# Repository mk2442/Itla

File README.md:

# Itla

Repositorio de proyectos y prácticas.

## Estructura

| Carpeta | Contenido |
|---|---|
| `solid/` | Diseños en SolidWorks: piezas, ensambles, planos y archivos de impresión 3D |
| `electronica/` | Proyectos de electrónica: placa ESP32-DEVKITV1 (librerías y documentación), PHM-30A y carrito (KiCad) |
| `programacion-c/` | Ejercicios y prácticas en lenguaje C, organizados por capítulo y proyecto |
| `digital/` | Circuitos digitales: proyectos (Gowin, KiCad, Proteus, RC), impresión 3D y documentos de clase |
| `microcontroladores/` | Proyectos de microcontroladores: ESP-IDF (ESP32) y Arduino |

Los archivos de compilación, binarios y configuración local del IDE no se incluyen.

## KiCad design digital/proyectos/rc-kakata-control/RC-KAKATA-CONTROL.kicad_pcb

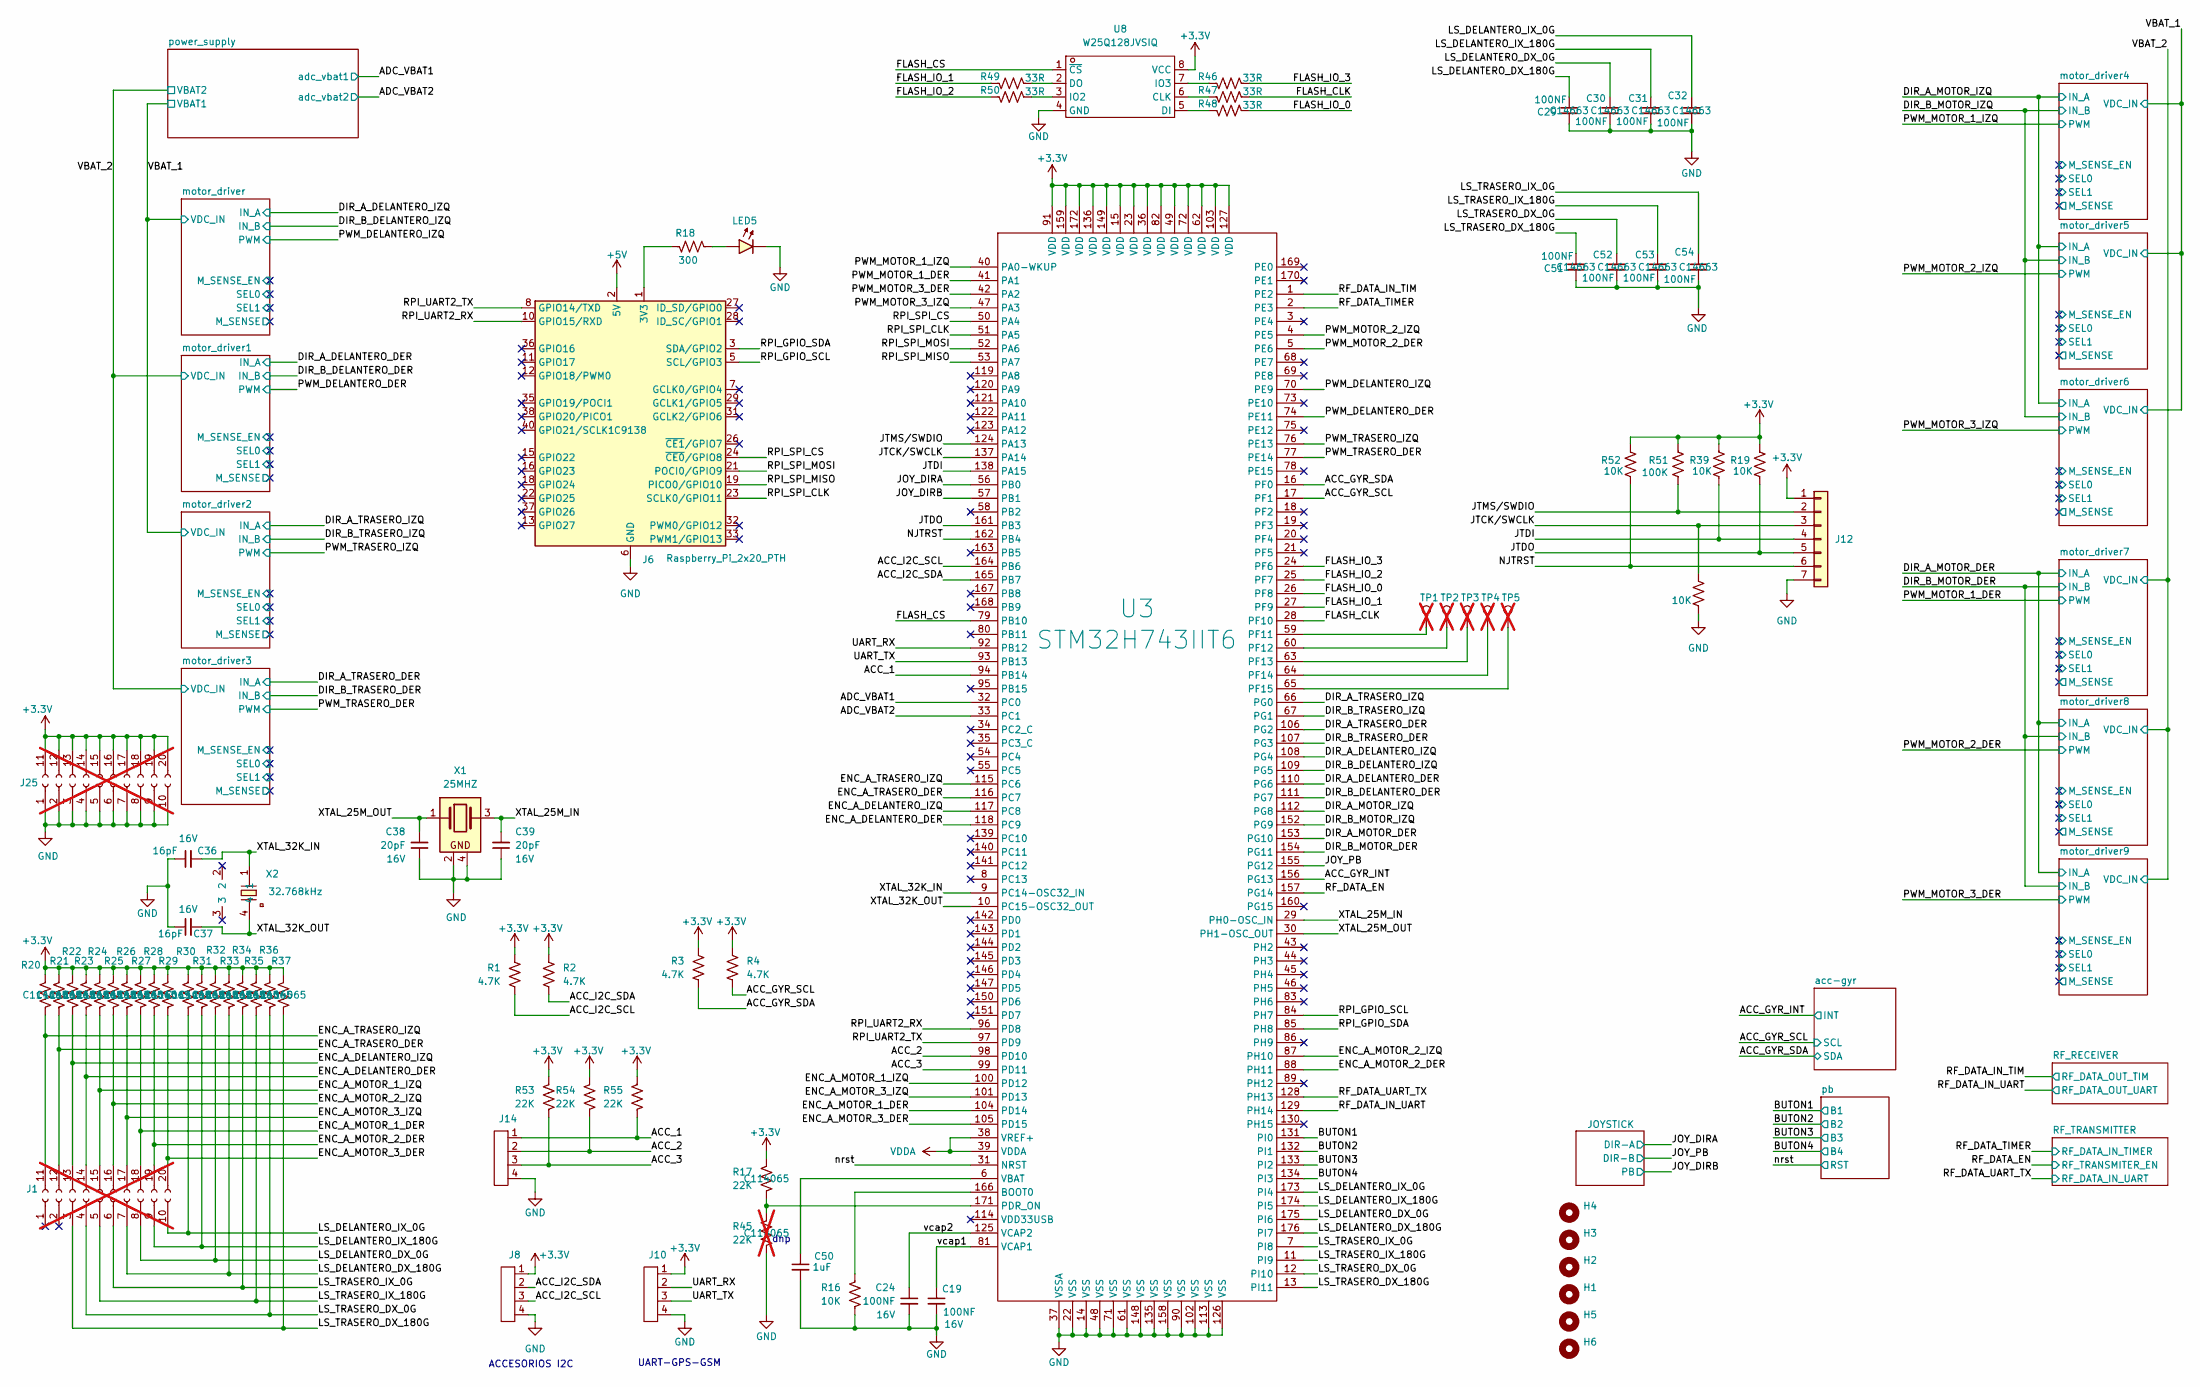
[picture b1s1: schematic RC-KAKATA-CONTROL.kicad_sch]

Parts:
C19, C24, C29, C30, C31, C32, C51, C52, C53, C54: 100NF; C_0603; Part Number 0603YC104KAT2A; JLCPCB ID C14663
C36, C37: 16pF; C_0603; Part Number 0603YC104KAT2A; JLCPCB ID C14663
C38, C39: 20pF; C_0603; Part Number 0603YC104KAT2A; JLCPCB ID C14663
C50: 1uF; C_0603; Part Number 0603YC104KAT2A; JLCPCB ID C14663
H1, H2, H3, H4, H5, H6: MountingHole; MountingHole_3.2mm_M3
J1, J25: Conn_02x20_Socket_DG250T-5.0-20P; DG250T-5.0-20P; not fitted
J6: Raspberry_Pi_2x20_PTH; 2x20_Shrouded; LCSC Part C9138
J8, J10, J14: DB125-2.54-4P-GN; CONN-TH_DB125-2.54-4P-GN; LCSC Part C918122
J12: Conn_01x07; PinHeader_1x07_P2.54mm_Vertical; LCSC Part C6332200
LED5: LED_0603_Red; LED_0603_1608Metric; LCSC Part C965799
R1, R2, R3, R4: 4.7K; R_0603; Part Number RC0603FR-0710KL; LCSC Part C99782
R16, R19, R38, R39, R52: 10K; R_0603; Part Number RC0603FR-0710KL; LCSC Part C98220
R17, R20, R21, R22, R23, R24, R25, R26, R27, R28, R29, R30, R31, R32, R33, R34, R35, R36, R37, R53, R54, R55: 22K; R_0603; Part Number RC0603FR-0710KL; LCSC Part C114065
R18: 300; R_0603; Part Number RC0603FR-0710KL; LCSC Part C114617
R45: 22K; R_0603; Part Number RC0603FR-0710KL; LCSC Part C114065; not fitted
R46, R47, R48, R49, R50: 33R; R_0603; Part Number RC0603FR-0710KL; LCSC Part C108661
R51: 100K; R_0603; Part Number RC0603FR-0710KL; LCSC Part C14675
TP1, TP2, TP3, TP4, TP5: TestPoint_Hole1; TestPoint_WireHole; not fitted
U3: STM32H743IIT6; LQFP-176_L24.0-W24.0-P0.50-LS26.0-BL; LCSC Part C89597
U8: W25Q128JVSIQ; SOIC-8_L5.3-W5.3-P1.27-LS8.0-BL; LCSC Part C97521
X1: 25MHZ; Crystal_SMD_3225-4Pin_3.2x2.5mm; PART_NUMBER XL2EL89CSI-111YLC-25M; LCSC Part C5280577
X2: 32.768kHz; MC-306_4P-L8.0-W3.2-P5.5-BL; PART_NUMBER Q13MC30610003; LCSC Part C16320

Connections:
+3.3V: J8.1, J10.1, J12.1, J25.11 (Pin_1), J25.12 (Pin_2), J25.13 (Pin_3), J25.14 (Pin_4), J25.15 (Pin_5), J25.16 (Pin_6), J25.17 (Pin_7), J25.18 (Pin_8), J25.19 (Pin_9), J25.20 (Pin_10), R1.1, R2.1, R3.1, R4.1, R17.1, R19.1, R20.1, R21.1, R22.1, R23.1, R24.1, R25.1, R26.1, R27.1, R28.1, R29.1, R30.1, R31.1, R32.1, R33.1, R34.1, R35.1, R36.1, R37.1, R39.1, R51.1, R52.1, R53.1, R54.1, R55.1, U3.15 (VDD), U3.23 (VDD), U3.36 (VDD), U3.49 (VDD), U3.62 (VDD), U3.72 (VDD), U3.82 (VDD), U3.91 (VDD), U3.103 (VDD), U3.127 (VDD), U3.136 (VDD), U3.149 (VDD), U3.159 (VDD), U3.172 (VDD), U8.8 (VCC); also elsewhere on the board
+5V: J6.2 (5V), J6.4 (5V); also elsewhere on the board
/ACC_1: J14.1, R55.2, U3.94 (PB14)
/ACC_2: J14.2, R54.2, U3.98 (PD10)
/ACC_3: J14.3, R53.2, U3.99 (PD11)
/ACC_GYR_INT: U3.156 (PG13); also elsewhere on the board
/ACC_GYR_SCL: R4.2, U3.17 (PF1); also elsewhere on the board
/ACC_GYR_SDA: R3.2, U3.16 (PF0); also elsewhere on the board
/ACC_I2C_SCL: J8.3, R1.2, U3.164 (PB6)
/ACC_I2C_SDA: J8.2, R2.2, U3.165 (PB7)
/ADC_VBAT1: U3.32 (PC0); also elsewhere on the board
/ADC_VBAT2: U3.33 (PC1); also elsewhere on the board
/BUTON1: U3.131 (PI0); also elsewhere on the board
/BUTON2: U3.132 (PI1); also elsewhere on the board
/BUTON3: U3.133 (PI2); also elsewhere on the board
/BUTON4: U3.134 (PI3); also elsewhere on the board
/DIR_A_DELANTERO_DER: U3.110 (PG6); also elsewhere on the board
/DIR_A_DELANTERO_IZQ: U3.108 (PG4); also elsewhere on the board
/DIR_A_MOTOR_DER: U3.153 (PG10); also elsewhere on the board
/DIR_A_MOTOR_IZQ: U3.112 (PG8); also elsewhere on the board
/DIR_A_TRASERO_DER: U3.106 (PG2); also elsewhere on the board
/DIR_A_TRASERO_IZQ: U3.66 (PG0); also elsewhere on the board
/DIR_B_DELANTERO_DER: U3.111 (PG7); also elsewhere on the board
/DIR_B_DELANTERO_IZQ: U3.109 (PG5); also elsewhere on the board
/DIR_B_MOTOR_DER: U3.154 (PG11); also elsewhere on the board
/DIR_B_MOTOR_IZQ: U3.152 (PG9); also elsewhere on the board
/DIR_B_TRASERO_DER: U3.107 (PG3); also elsewhere on the board
/DIR_B_TRASERO_IZQ: U3.67 (PG1); also elsewhere on the board
/ENC_A_DELANTERO_DER: J1.14 (Pin_4), R23.2, U3.118 (PC9)
/ENC_A_DELANTERO_IZQ: J1.13 (Pin_3), R22.2, U3.117 (PC8)
/ENC_A_MOTOR_1_DER: J1.18 (Pin_8), R27.2, U3.104 (PD14)
/ENC_A_MOTOR_1_IZQ: J1.15 (Pin_5), R24.2, U3.100 (PD12)
/ENC_A_MOTOR_2_DER: J1.19 (Pin_9), R28.2, U3.88 (PH11)
/ENC_A_MOTOR_2_IZQ: J1.16 (Pin_6), R25.2, U3.87 (PH10)
/ENC_A_MOTOR_3_DER: J1.20 (Pin_10), R29.2, U3.105 (PD15)
/ENC_A_MOTOR_3_IZQ: J1.17 (Pin_7), R26.2, U3.101 (PD13)
/ENC_A_TRASERO_DER: J1.12 (Pin_2), R21.2, U3.116 (PC7)
/ENC_A_TRASERO_IZQ: J1.11 (Pin_1), R20.2, U3.115 (PC6)
/FLASH_CLK: R47.2, U3.28 (PF10)
/FLASH_CS: U3.79 (PB10), U8.1 (~CS)
/FLASH_IO_0: R48.2, U3.26 (PF8)
/FLASH_IO_1: R49.1, U3.27 (PF9)
/FLASH_IO_2: R50.1, U3.25 (PF7)
/FLASH_IO_3: R46.2, U3.24 (PF6)
/JOY_DIRA: U3.56 (PB0); also elsewhere on the board
/JOY_DIRB: U3.57 (PB1); also elsewhere on the board
/JOY_PB: U3.155 (PG12); also elsewhere on the board
/JTCK/SWCLK: J12.3, R38.1, U3.137 (PA14)
/JTDI: J12.4, R39.2, U3.138 (PA15)
/JTDO: J12.5, R19.2, U3.161 (PB3)
/JTMS/SWDIO: J12.2, R51.2, U3.124 (PA13)
/LS_DELANTERO_DX_0G: C30.1, J1.8, R32.2, U3.175 (PI6)
/LS_DELANTERO_DX_180G: C29.1, J1.7, R33.2, U3.176 (PI7)
/LS_DELANTERO_IX_0G: C32.1, J1.10, R30.2, U3.173 (PI4)
/LS_DELANTERO_IX_180G: C31.1, J1.9, R31.2, U3.174 (PI5)
/LS_TRASERO_DX_0G: C52.1, J1.4, R36.2, U3.12 (PI10)
/LS_TRASERO_DX_180G: C51.1, J1.3, R37.2, U3.13 (PI11)
/LS_TRASERO_IX_0G: C54.1, J1.6, R34.2, U3.7 (PI8)
/LS_TRASERO_IX_180G: C53.1, J1.5, R35.2, U3.11 (PI9)
/NJTRST: J12.6, R52.2, U3.162 (PB4)
/PWM_DELANTERO_DER: U3.74 (PE11); also elsewhere on the board
/PWM_DELANTERO_IZQ: U3.70 (PE9); also elsewhere on the board
/PWM_MOTOR_1_DER: U3.41 (PA1); also elsewhere on the board
/PWM_MOTOR_1_IZQ: U3.40 (PA0-WKUP); also elsewhere on the board
/PWM_MOTOR_2_DER: U3.5 (PE6); also elsewhere on the board
/PWM_MOTOR_2_IZQ: U3.4 (PE5); also elsewhere on the board
/PWM_MOTOR_3_DER: U3.42 (PA2); also elsewhere on the board
/PWM_MOTOR_3_IZQ: U3.47 (PA3); also elsewhere on the board
/PWM_TRASERO_DER: U3.77 (PE14); also elsewhere on the board
/PWM_TRASERO_IZQ: U3.76 (PE13); also elsewhere on the board
/RF_DATA_EN: U3.157 (PG14); also elsewhere on the board
/RF_DATA_IN_TIM: U3.1 (PE2); also elsewhere on the board
/RF_DATA_IN_UART: U3.129 (PH14); also elsewhere on the board
/RF_DATA_TIMER: U3.2 (PE3); also elsewhere on the board
/RF_DATA_UART_TX: U3.128 (PH13); also elsewhere on the board
/RPI_GPIO_SCL: J6.5 (SCL/GPIO3), U3.84 (PH7)
/RPI_GPIO_SDA: J6.3 (SDA/GPIO2), U3.85 (PH8)
/RPI_SPI_CLK: J6.23 (SCLK0/GPIO11), U3.51 (PA5)
/RPI_SPI_CS: J6.24 (~CE0/GPIO8), U3.50 (PA4)
/RPI_SPI_MISO: J6.19 (PICO0/GPIO10), U3.53 (PA7)
/RPI_SPI_MOSI: J6.21 (POCI0/GPIO9), U3.52 (PA6)
/RPI_UART2_RX: J6.10 (GPIO15/RXD), U3.96 (PD8)
/RPI_UART2_TX: J6.8 (GPIO14/TXD), U3.97 (PD9)
/UART_RX: J10.2, U3.92 (PB12)
/UART_TX: J10.3, U3.93 (PB13)
/XTAL_25M_IN: C39.2, U3.29 (PH0-OSC_IN), X1.3
/XTAL_25M_OUT: C38.2, U3.30 (PH1-OSC_OUT), X1.1
/XTAL_32K_IN: C36.2, U3.9 (PC14-OSC32_IN), X2.1
/XTAL_32K_OUT: C37.2, U3.10 (PC15-OSC32_OUT), X2.4
/nrst: U3.31 (NRST); also elsewhere on the board
/vcap1: C19.1, U3.81 (VCAP1)
/vcap2: C24.1, U3.125 (VCAP2)
GND: C19.2, C24.2, C29.2, C30.2, C31.2, C32.2, C36.1, C37.1, C38.1, C39.1, C50.2, C51.2, C52.2, C53.2, C54.2, J6.6 (GND), J6.9 (GND), J6.14 (GND), J6.20 (GND), J6.25 (GND), J6.30 (GND), J6.34 (GND), J6.39 (GND), J8.4, J10.4, J12.7, J14.4, J25.1, J25.2, J25.3, J25.4, J25.5, J25.6, J25.7, J25.8, J25.9, J25.10, LED5.1 (K), R16.2, R38.2, R45.2, U3.14 (VSS), U3.22 (VSS), U3.37 (VSSA), U3.48 (VSS), U3.61 (VSS), U3.71 (VSS), U3.90 (VSS), U3.102 (VSS), U3.113 (VSS), U3.126 (VSS), U3.135 (VSS), U3.148 (VSS), U3.158 (VSS), U8.4 (GND), X1.2, X1.4; also elsewhere on the board
unnamed: J6.1 (3V3), J6.17 (3V3), R18.1
unnamed: LED5.2 (A), R18.2
unnamed: R16.1, U3.166 (BOOT0)
unnamed: R17.2, R45.1, U3.171 (PDR_ON)
unnamed: TP1.1, U3.59 (PF11)
unnamed: TP2.1, U3.60 (PF12)
unnamed: TP3.1, U3.63 (PF13)
unnamed: TP4.1, U3.64 (PF14)
unnamed: TP5.1, U3.65 (PF15)
unnamed: C50.1, U3.6 (VBAT)
unnamed: R47.1, U8.6 (CLK)
unnamed: R48.1, U8.5 (DI)
unnamed: R49.2, U8.2 (DO)
unnamed: R50.2, U8.3 (IO2)
unnamed: R46.1, U8.7 (IO3)
VDDA: U3.38 (VREF+), U3.39 (VDDA); also elsewhere on the board

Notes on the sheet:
UART-GPS-GSM
ACCESORIOS I2C
dnp

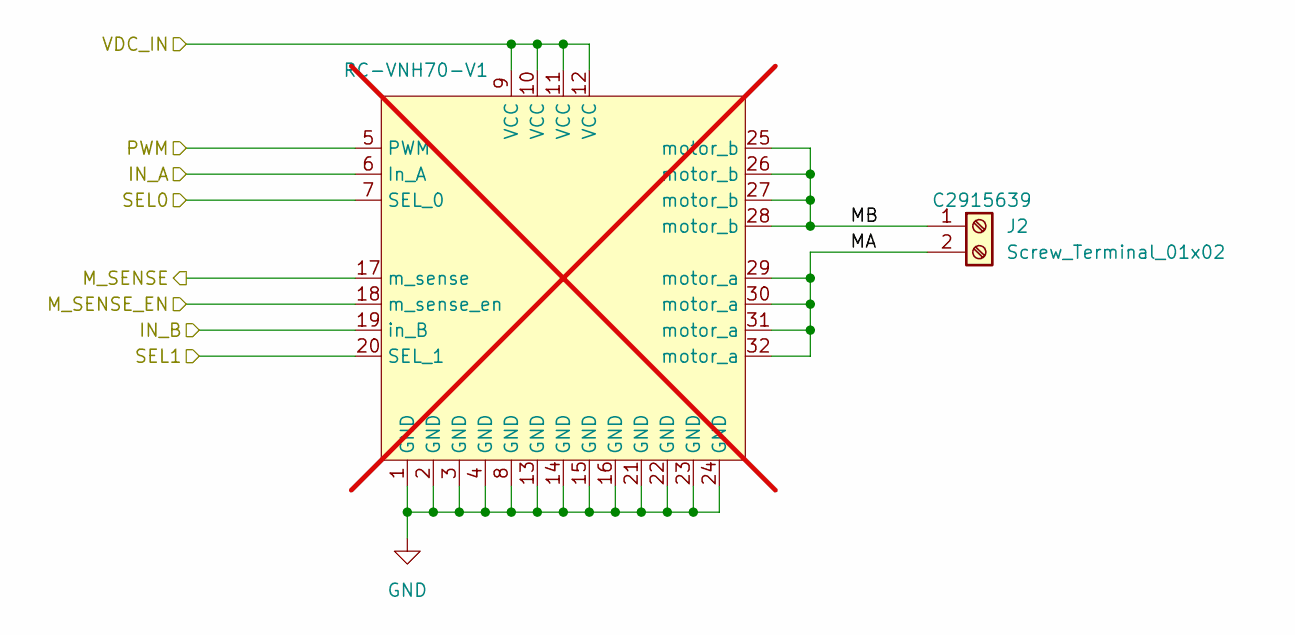
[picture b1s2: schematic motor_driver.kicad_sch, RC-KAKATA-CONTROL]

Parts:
J2: Screw_Terminal_01x02; CONN-TH_2P-P5.08_DIBO_DB128V-5.08; LCSC PN C2915639
RC-VNH70-V1: RC-VNH70-V1; not fitted

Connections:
/DIR_A_DELANTERO_IZQ: RC-VNH70-V1.6 (In_A); also elsewhere on the board
/DIR_B_DELANTERO_IZQ: RC-VNH70-V1.19 (in_B); also elsewhere on the board
/PWM_DELANTERO_IZQ: RC-VNH70-V1.5 (PWM); also elsewhere on the board
/VBAT_1: RC-VNH70-V1.9 (VCC), RC-VNH70-V1.10 (VCC), RC-VNH70-V1.11 (VCC), RC-VNH70-V1.12 (VCC); also elsewhere on the board
/motor_driver/MA: J2.2, RC-VNH70-V1.29 (motor_a), RC-VNH70-V1.30 (motor_a), RC-VNH70-V1.31 (motor_a), RC-VNH70-V1.32 (motor_a)
/motor_driver/MB: J2.1, RC-VNH70-V1.25 (motor_b), RC-VNH70-V1.26 (motor_b), RC-VNH70-V1.27 (motor_b), RC-VNH70-V1.28 (motor_b)
/motor_driver/M_SENSE: RC-VNH70-V1.17 (m_sense)
/motor_driver/M_SENSE_EN: RC-VNH70-V1.18 (m_sense_en)
/motor_driver/SEL0: RC-VNH70-V1.7 (SEL_0)
/motor_driver/SEL1: RC-VNH70-V1.20 (SEL_1)
GND: RC-VNH70-V1.1 (GND), RC-VNH70-V1.2 (GND), RC-VNH70-V1.3 (GND), RC-VNH70-V1.4 (GND), RC-VNH70-V1.8 (GND), RC-VNH70-V1.13 (GND), RC-VNH70-V1.14 (GND), RC-VNH70-V1.15 (GND), RC-VNH70-V1.16 (GND), RC-VNH70-V1.21 (GND), RC-VNH70-V1.22 (GND), RC-VNH70-V1.23 (GND), RC-VNH70-V1.24 (GND); also elsewhere on the board

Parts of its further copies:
J5, J7, J9, J11, J13, J17, J19, J21, J23: Screw_Terminal_01x02; CONN-TH_2P-P5.08_DIBO_DB128V-5.08; LCSC PN C2915639
RC-VNH70-V2, RC-VNH70-V3, RC-VNH70-V4, RC-VNH70-V5, RC-VNH70-V6, RC-VNH70-V7, RC-VNH70-V8, RC-VNH70-V9, RC-VNH70-V10: RC-VNH70-V1; not fitted

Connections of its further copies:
/DIR_A_DELANTERO_DER: RC-VNH70-V2.6 (In_A); also elsewhere on the board
/DIR_A_MOTOR_DER: RC-VNH70-V8.6 (In_A), RC-VNH70-V9.6 (In_A), RC-VNH70-V10.6 (In_A); also elsewhere on the board
/DIR_A_MOTOR_IZQ: RC-VNH70-V5.6 (In_A), RC-VNH70-V6.6 (In_A), RC-VNH70-V7.6 (In_A); also elsewhere on the board
/DIR_A_TRASERO_DER: RC-VNH70-V4.6 (In_A); also elsewhere on the board
/DIR_A_TRASERO_IZQ: RC-VNH70-V3.6 (In_A); also elsewhere on the board
/DIR_B_DELANTERO_DER: RC-VNH70-V2.19 (in_B); also elsewhere on the board
/DIR_B_MOTOR_DER: RC-VNH70-V8.19 (in_B), RC-VNH70-V9.19 (in_B), RC-VNH70-V10.19 (in_B); also elsewhere on the board
/DIR_B_MOTOR_IZQ: RC-VNH70-V5.19 (in_B), RC-VNH70-V6.19 (in_B), RC-VNH70-V7.19 (in_B); also elsewhere on the board
/DIR_B_TRASERO_DER: RC-VNH70-V4.19 (in_B); also elsewhere on the board
/DIR_B_TRASERO_IZQ: RC-VNH70-V3.19 (in_B); also elsewhere on the board
/PWM_DELANTERO_DER: RC-VNH70-V2.5 (PWM); also elsewhere on the board
/PWM_MOTOR_1_DER: RC-VNH70-V8.5 (PWM); also elsewhere on the board
/PWM_MOTOR_1_IZQ: RC-VNH70-V5.5 (PWM); also elsewhere on the board
/PWM_MOTOR_2_DER: RC-VNH70-V9.5 (PWM); also elsewhere on the board
/PWM_MOTOR_2_IZQ: RC-VNH70-V6.5 (PWM); also elsewhere on the board
/PWM_MOTOR_3_DER: RC-VNH70-V10.5 (PWM); also elsewhere on the board
/PWM_MOTOR_3_IZQ: RC-VNH70-V7.5 (PWM); also elsewhere on the board
/PWM_TRASERO_DER: RC-VNH70-V4.5 (PWM); also elsewhere on the board
/PWM_TRASERO_IZQ: RC-VNH70-V3.5 (PWM); also elsewhere on the board
/VBAT_1: RC-VNH70-V3.9 (VCC), RC-VNH70-V3.10 (VCC), RC-VNH70-V3.11 (VCC), RC-VNH70-V3.12 (VCC), RC-VNH70-V5.9 (VCC), RC-VNH70-V5.10 (VCC), RC-VNH70-V5.11 (VCC), RC-VNH70-V5.12 (VCC), RC-VNH70-V6.9 (VCC), RC-VNH70-V6.10 (VCC), RC-VNH70-V6.11 (VCC), RC-VNH70-V6.12 (VCC), RC-VNH70-V7.9 (VCC), RC-VNH70-V7.10 (VCC), RC-VNH70-V7.11 (VCC), RC-VNH70-V7.12 (VCC); also elsewhere on the board
/VBAT_2: RC-VNH70-V2.9 (VCC), RC-VNH70-V2.10 (VCC), RC-VNH70-V2.11 (VCC), RC-VNH70-V2.12 (VCC), RC-VNH70-V4.9 (VCC), RC-VNH70-V4.10 (VCC), RC-VNH70-V4.11 (VCC), RC-VNH70-V4.12 (VCC), RC-VNH70-V8.9 (VCC), RC-VNH70-V8.10 (VCC), RC-VNH70-V8.11 (VCC), RC-VNH70-V8.12 (VCC), RC-VNH70-V9.9 (VCC), RC-VNH70-V9.10 (VCC), RC-VNH70-V9.11 (VCC), RC-VNH70-V9.12 (VCC), RC-VNH70-V10.9 (VCC), RC-VNH70-V10.10 (VCC), RC-VNH70-V10.11 (VCC), RC-VNH70-V10.12 (VCC); also elsewhere on the board
/motor_driver1/MA: J5.2, RC-VNH70-V2.29 (motor_a), RC-VNH70-V2.30 (motor_a), RC-VNH70-V2.31 (motor_a), RC-VNH70-V2.32 (motor_a)
/motor_driver1/MB: J5.1, RC-VNH70-V2.25 (motor_b), RC-VNH70-V2.26 (motor_b), RC-VNH70-V2.27 (motor_b), RC-VNH70-V2.28 (motor_b)
/motor_driver1/M_SENSE: RC-VNH70-V2.17 (m_sense)
/motor_driver1/M_SENSE_EN: RC-VNH70-V2.18 (m_sense_en)
/motor_driver1/SEL0: RC-VNH70-V2.7 (SEL_0)
/motor_driver1/SEL1: RC-VNH70-V2.20 (SEL_1)
/motor_driver2/MA: J7.2, RC-VNH70-V3.29 (motor_a), RC-VNH70-V3.30 (motor_a), RC-VNH70-V3.31 (motor_a), RC-VNH70-V3.32 (motor_a)
/motor_driver2/MB: J7.1, RC-VNH70-V3.25 (motor_b), RC-VNH70-V3.26 (motor_b), RC-VNH70-V3.27 (motor_b), RC-VNH70-V3.28 (motor_b)
/motor_driver2/M_SENSE: RC-VNH70-V3.17 (m_sense)
/motor_driver2/M_SENSE_EN: RC-VNH70-V3.18 (m_sense_en)
/motor_driver2/SEL0: RC-VNH70-V3.7 (SEL_0)
/motor_driver2/SEL1: RC-VNH70-V3.20 (SEL_1)
/motor_driver3/MA: J9.2, RC-VNH70-V4.29 (motor_a), RC-VNH70-V4.30 (motor_a), RC-VNH70-V4.31 (motor_a), RC-VNH70-V4.32 (motor_a)
/motor_driver3/MB: J9.1, RC-VNH70-V4.25 (motor_b), RC-VNH70-V4.26 (motor_b), RC-VNH70-V4.27 (motor_b), RC-VNH70-V4.28 (motor_b)
/motor_driver3/M_SENSE: RC-VNH70-V4.17 (m_sense)
/motor_driver3/M_SENSE_EN: RC-VNH70-V4.18 (m_sense_en)
/motor_driver3/SEL0: RC-VNH70-V4.7 (SEL_0)
/motor_driver3/SEL1: RC-VNH70-V4.20 (SEL_1)
/motor_driver4/MA: J11.2, RC-VNH70-V5.29 (motor_a), RC-VNH70-V5.30 (motor_a), RC-VNH70-V5.31 (motor_a), RC-VNH70-V5.32 (motor_a)
/motor_driver4/MB: J11.1, RC-VNH70-V5.25 (motor_b), RC-VNH70-V5.26 (motor_b), RC-VNH70-V5.27 (motor_b), RC-VNH70-V5.28 (motor_b)
/motor_driver4/M_SENSE: RC-VNH70-V5.17 (m_sense)
/motor_driver4/M_SENSE_EN: RC-VNH70-V5.18 (m_sense_en)
/motor_driver4/SEL0: RC-VNH70-V5.7 (SEL_0)
/motor_driver4/SEL1: RC-VNH70-V5.20 (SEL_1)
/motor_driver5/MA: J13.2, RC-VNH70-V6.29 (motor_a), RC-VNH70-V6.30 (motor_a), RC-VNH70-V6.31 (motor_a), RC-VNH70-V6.32 (motor_a)
/motor_driver5/MB: J13.1, RC-VNH70-V6.25 (motor_b), RC-VNH70-V6.26 (motor_b), RC-VNH70-V6.27 (motor_b), RC-VNH70-V6.28 (motor_b)
/motor_driver5/M_SENSE: RC-VNH70-V6.17 (m_sense)
/motor_driver5/M_SENSE_EN: RC-VNH70-V6.18 (m_sense_en)
/motor_driver5/SEL0: RC-VNH70-V6.7 (SEL_0)
/motor_driver5/SEL1: RC-VNH70-V6.20 (SEL_1)
/motor_driver6/MA: J17.2, RC-VNH70-V7.29 (motor_a), RC-VNH70-V7.30 (motor_a), RC-VNH70-V7.31 (motor_a), RC-VNH70-V7.32 (motor_a)
/motor_driver6/MB: J17.1, RC-VNH70-V7.25 (motor_b), RC-VNH70-V7.26 (motor_b), RC-VNH70-V7.27 (motor_b), RC-VNH70-V7.28 (motor_b)
/motor_driver6/M_SENSE: RC-VNH70-V7.17 (m_sense)
/motor_driver6/M_SENSE_EN: RC-VNH70-V7.18 (m_sense_en)
/motor_driver6/SEL0: RC-VNH70-V7.7 (SEL_0)
/motor_driver6/SEL1: RC-VNH70-V7.20 (SEL_1)
/motor_driver7/MA: J19.2, RC-VNH70-V8.29 (motor_a), RC-VNH70-V8.30 (motor_a), RC-VNH70-V8.31 (motor_a), RC-VNH70-V8.32 (motor_a)
/motor_driver7/MB: J19.1, RC-VNH70-V8.25 (motor_b), RC-VNH70-V8.26 (motor_b), RC-VNH70-V8.27 (motor_b), RC-VNH70-V8.28 (motor_b)
/motor_driver7/M_SENSE: RC-VNH70-V8.17 (m_sense)
/motor_driver7/M_SENSE_EN: RC-VNH70-V8.18 (m_sense_en)
/motor_driver7/SEL0: RC-VNH70-V8.7 (SEL_0)
/motor_driver7/SEL1: RC-VNH70-V8.20 (SEL_1)
/motor_driver8/MA: J21.2, RC-VNH70-V9.29 (motor_a), RC-VNH70-V9.30 (motor_a), RC-VNH70-V9.31 (motor_a), RC-VNH70-V9.32 (motor_a)
/motor_driver8/MB: J21.1, RC-VNH70-V9.25 (motor_b), RC-VNH70-V9.26 (motor_b), RC-VNH70-V9.27 (motor_b), RC-VNH70-V9.28 (motor_b)
/motor_driver8/M_SENSE: RC-VNH70-V9.17 (m_sense)
/motor_driver8/M_SENSE_EN: RC-VNH70-V9.18 (m_sense_en)
/motor_driver8/SEL0: RC-VNH70-V9.7 (SEL_0)
/motor_driver8/SEL1: RC-VNH70-V9.20 (SEL_1)
/motor_driver9/MA: J23.2, RC-VNH70-V10.29 (motor_a), RC-VNH70-V10.30 (motor_a), RC-VNH70-V10.31 (motor_a), RC-VNH70-V10.32 (motor_a)
/motor_driver9/MB: J23.1, RC-VNH70-V10.25 (motor_b), RC-VNH70-V10.26 (motor_b), RC-VNH70-V10.27 (motor_b), RC-VNH70-V10.28 (motor_b)
/motor_driver9/M_SENSE: RC-VNH70-V10.17 (m_sense)
/motor_driver9/M_SENSE_EN: RC-VNH70-V10.18 (m_sense_en)
/motor_driver9/SEL0: RC-VNH70-V10.7 (SEL_0)
/motor_driver9/SEL1: RC-VNH70-V10.20 (SEL_1)
GND: RC-VNH70-V2.1 (GND), RC-VNH70-V2.2 (GND), RC-VNH70-V2.3 (GND), RC-VNH70-V2.4 (GND), RC-VNH70-V2.8 (GND), RC-VNH70-V2.13 (GND), RC-VNH70-V2.14 (GND), RC-VNH70-V2.15 (GND), RC-VNH70-V2.16 (GND), RC-VNH70-V2.21 (GND), RC-VNH70-V2.22 (GND), RC-VNH70-V2.23 (GND), RC-VNH70-V2.24 (GND), RC-VNH70-V3.1 (GND), RC-VNH70-V3.2 (GND), RC-VNH70-V3.3 (GND), RC-VNH70-V3.4 (GND), RC-VNH70-V3.8 (GND), RC-VNH70-V3.13 (GND), RC-VNH70-V3.14 (GND), RC-VNH70-V3.15 (GND), RC-VNH70-V3.16 (GND), RC-VNH70-V3.21 (GND), RC-VNH70-V3.22 (GND), RC-VNH70-V3.23 (GND), RC-VNH70-V3.24 (GND), RC-VNH70-V4.1 (GND), RC-VNH70-V4.2 (GND), RC-VNH70-V4.3 (GND), RC-VNH70-V4.4 (GND), RC-VNH70-V4.8 (GND), RC-VNH70-V4.13 (GND), RC-VNH70-V4.14 (GND), RC-VNH70-V4.15 (GND), RC-VNH70-V4.16 (GND), RC-VNH70-V4.21 (GND), RC-VNH70-V4.22 (GND), RC-VNH70-V4.23 (GND), RC-VNH70-V4.24 (GND), RC-VNH70-V5.1 (GND), RC-VNH70-V5.2 (GND), RC-VNH70-V5.3 (GND), RC-VNH70-V5.4 (GND), RC-VNH70-V5.8 (GND), RC-VNH70-V5.13 (GND), RC-VNH70-V5.14 (GND), RC-VNH70-V5.15 (GND), RC-VNH70-V5.16 (GND), RC-VNH70-V5.21 (GND), RC-VNH70-V5.22 (GND), RC-VNH70-V5.23 (GND), RC-VNH70-V5.24 (GND), RC-VNH70-V6.1 (GND), RC-VNH70-V6.2 (GND), RC-VNH70-V6.3 (GND), RC-VNH70-V6.4 (GND), RC-VNH70-V6.8 (GND), RC-VNH70-V6.13 (GND), RC-VNH70-V6.14 (GND), RC-VNH70-V6.15 (GND), RC-VNH70-V6.16 (GND), RC-VNH70-V6.21 (GND), RC-VNH70-V6.22 (GND), RC-VNH70-V6.23 (GND), RC-VNH70-V6.24 (GND), RC-VNH70-V7.1 (GND), RC-VNH70-V7.2 (GND), RC-VNH70-V7.3 (GND), RC-VNH70-V7.4 (GND), RC-VNH70-V7.8 (GND), RC-VNH70-V7.13 (GND), RC-VNH70-V7.14 (GND), RC-VNH70-V7.15 (GND), RC-VNH70-V7.16 (GND), RC-VNH70-V7.21 (GND), RC-VNH70-V7.22 (GND), RC-VNH70-V7.23 (GND), RC-VNH70-V7.24 (GND), RC-VNH70-V8.1 (GND), RC-VNH70-V8.2 (GND), RC-VNH70-V8.3 (GND), RC-VNH70-V8.4 (GND), RC-VNH70-V8.8 (GND), RC-VNH70-V8.13 (GND), RC-VNH70-V8.14 (GND), RC-VNH70-V8.15 (GND), RC-VNH70-V8.16 (GND), RC-VNH70-V8.21 (GND), RC-VNH70-V8.22 (GND), RC-VNH70-V8.23 (GND), RC-VNH70-V8.24 (GND), RC-VNH70-V9.1 (GND), RC-VNH70-V9.2 (GND), RC-VNH70-V9.3 (GND), RC-VNH70-V9.4 (GND), RC-VNH70-V9.8 (GND), RC-VNH70-V9.13 (GND), RC-VNH70-V9.14 (GND), RC-VNH70-V9.15 (GND), RC-VNH70-V9.16 (GND), RC-VNH70-V9.21 (GND), RC-VNH70-V9.22 (GND), RC-VNH70-V9.23 (GND), RC-VNH70-V9.24 (GND), RC-VNH70-V10.1 (GND), RC-VNH70-V10.2 (GND), RC-VNH70-V10.3 (GND), RC-VNH70-V10.4 (GND), RC-VNH70-V10.8 (GND), RC-VNH70-V10.13 (GND), RC-VNH70-V10.14 (GND), RC-VNH70-V10.15 (GND), RC-VNH70-V10.16 (GND), RC-VNH70-V10.21 (GND), RC-VNH70-V10.22 (GND), RC-VNH70-V10.23 (GND), RC-VNH70-V10.24 (GND); also elsewhere on the board

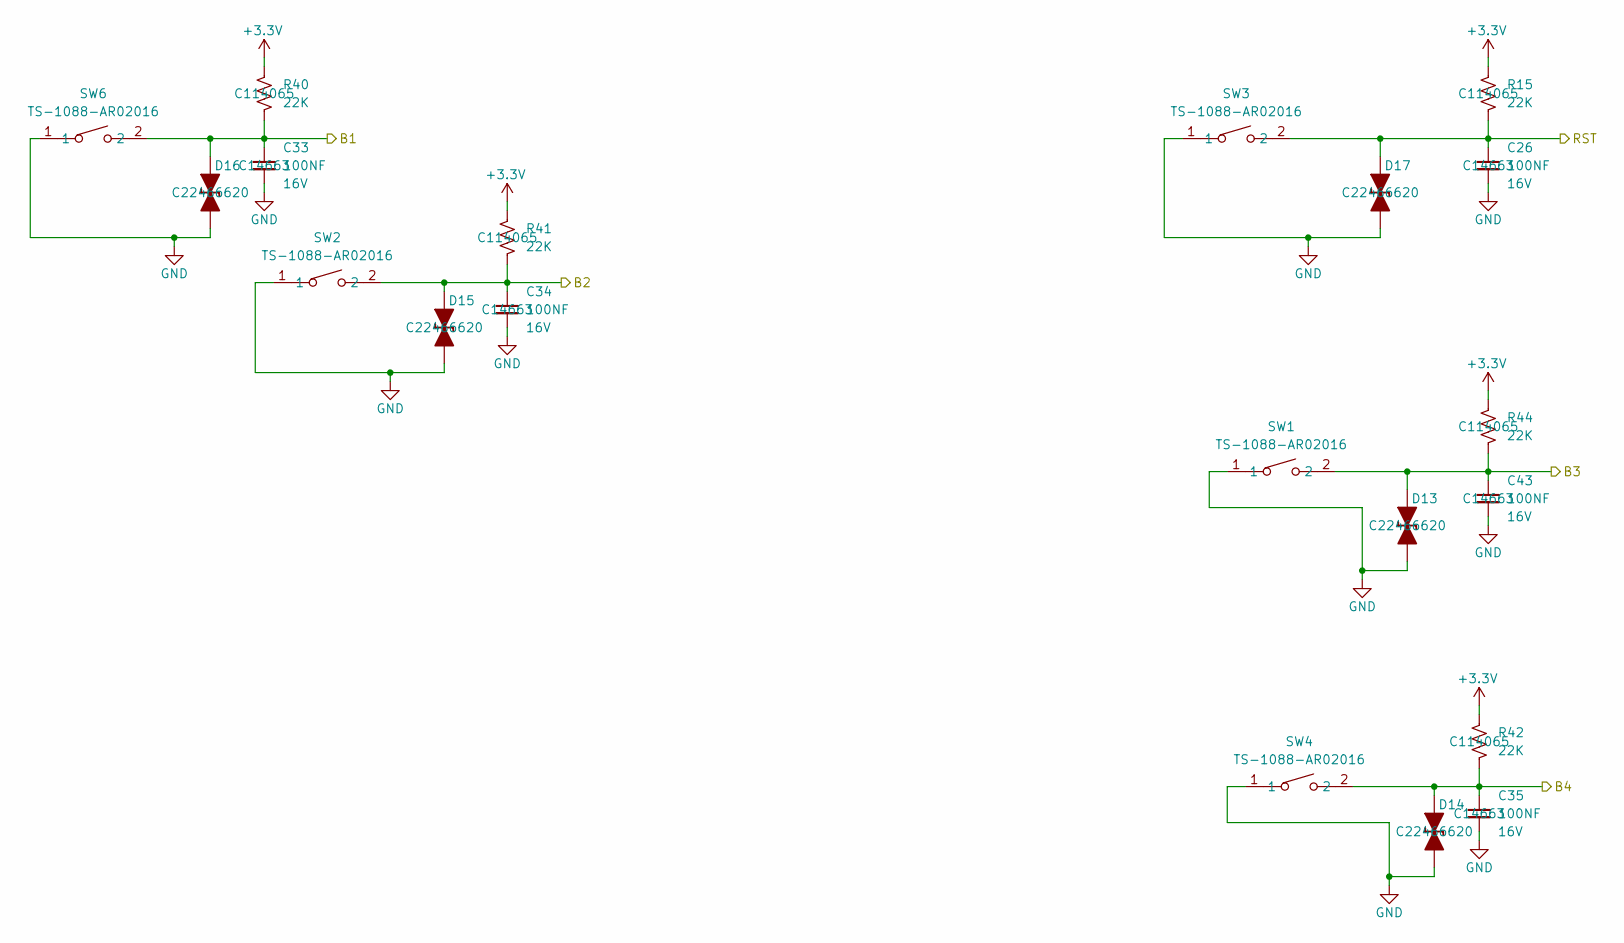
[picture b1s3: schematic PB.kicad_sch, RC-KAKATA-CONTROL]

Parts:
C26, C33, C34, C35, C43: 100NF; C_0603; Part Number 0603YC104KAT2A; JLCPCB ID C14663
D13, D14, D15, D16, D17: PESD3V3L1BA; D_SOD-323_TVS; LCSC Part C22466620
R15, R40, R41, R42, R44: 22K; R_0603; Part Number RC0603FR-0710KL; LCSC Part C114065
SW1, SW2, SW3, SW4, SW6: TS-1088-AR02016; SW-SMD_L3.9-W3.0-P4.45; LCSC Part C720477

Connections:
+3.3V: R15.1, R40.1, R41.1, R42.1, R44.1; also elsewhere on the board
/BUTON1: C33.1, D16.2 (A), R40.2, SW6.2; also elsewhere on the board
/BUTON2: C34.1, D15.2 (A), R41.2, SW2.2; also elsewhere on the board
/BUTON3: C43.1, D13.2 (A), R44.2, SW1.2; also elsewhere on the board
/BUTON4: C35.1, D14.2 (A), R42.2, SW4.2; also elsewhere on the board
/nrst: C26.1, D17.2 (A), R15.2, SW3.2; also elsewhere on the board
GND: C26.2, C33.2, C34.2, C35.2, C43.2, D13.1 (K), D14.1 (K), D15.1 (K), D16.1 (K), D17.1 (K), SW1.1, SW2.1, SW3.1, SW4.1, SW6.1; also elsewhere on the board

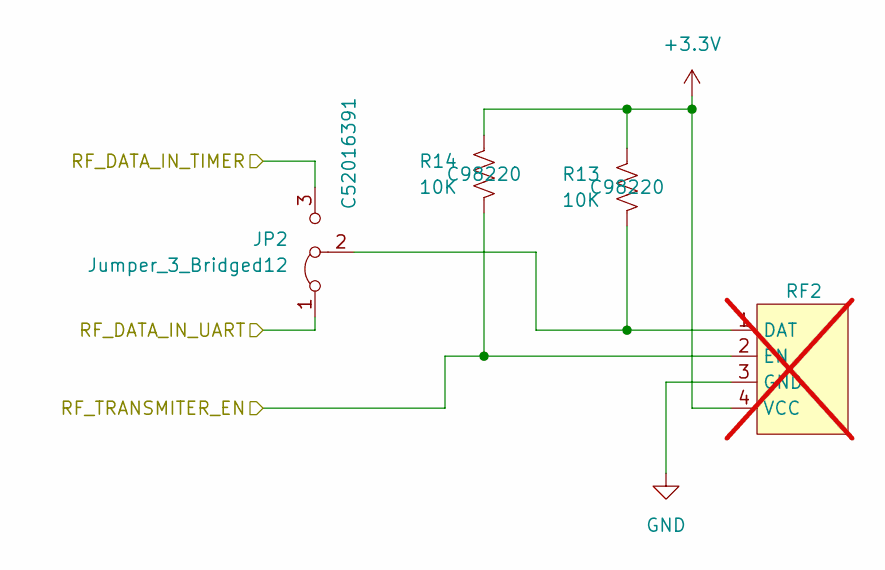
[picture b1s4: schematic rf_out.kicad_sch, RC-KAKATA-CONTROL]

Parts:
JP2: Jumper_3_Bridged12; PinHeader_1x03_P2.54mm_Vertical; LCSC Part C52016391
R13, R14: 10K; R_0603; Part Number RC0603FR-0710KL; LCSC Part C98220
RF2: Itla_RC_RF_433MHz_transmitter; not fitted

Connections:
+3.3V: R13.1, R14.1, RF2.4 (VCC); also elsewhere on the board
/RF_DATA_EN: R14.2, RF2.2 (EN); also elsewhere on the board
/RF_DATA_TIMER: JP2.3 (B); also elsewhere on the board
/RF_DATA_UART_TX: JP2.1 (A); also elsewhere on the board
GND: RF2.3 (GND); also elsewhere on the board
unnamed: JP2.2 (C), R13.2, RF2.1 (DAT)

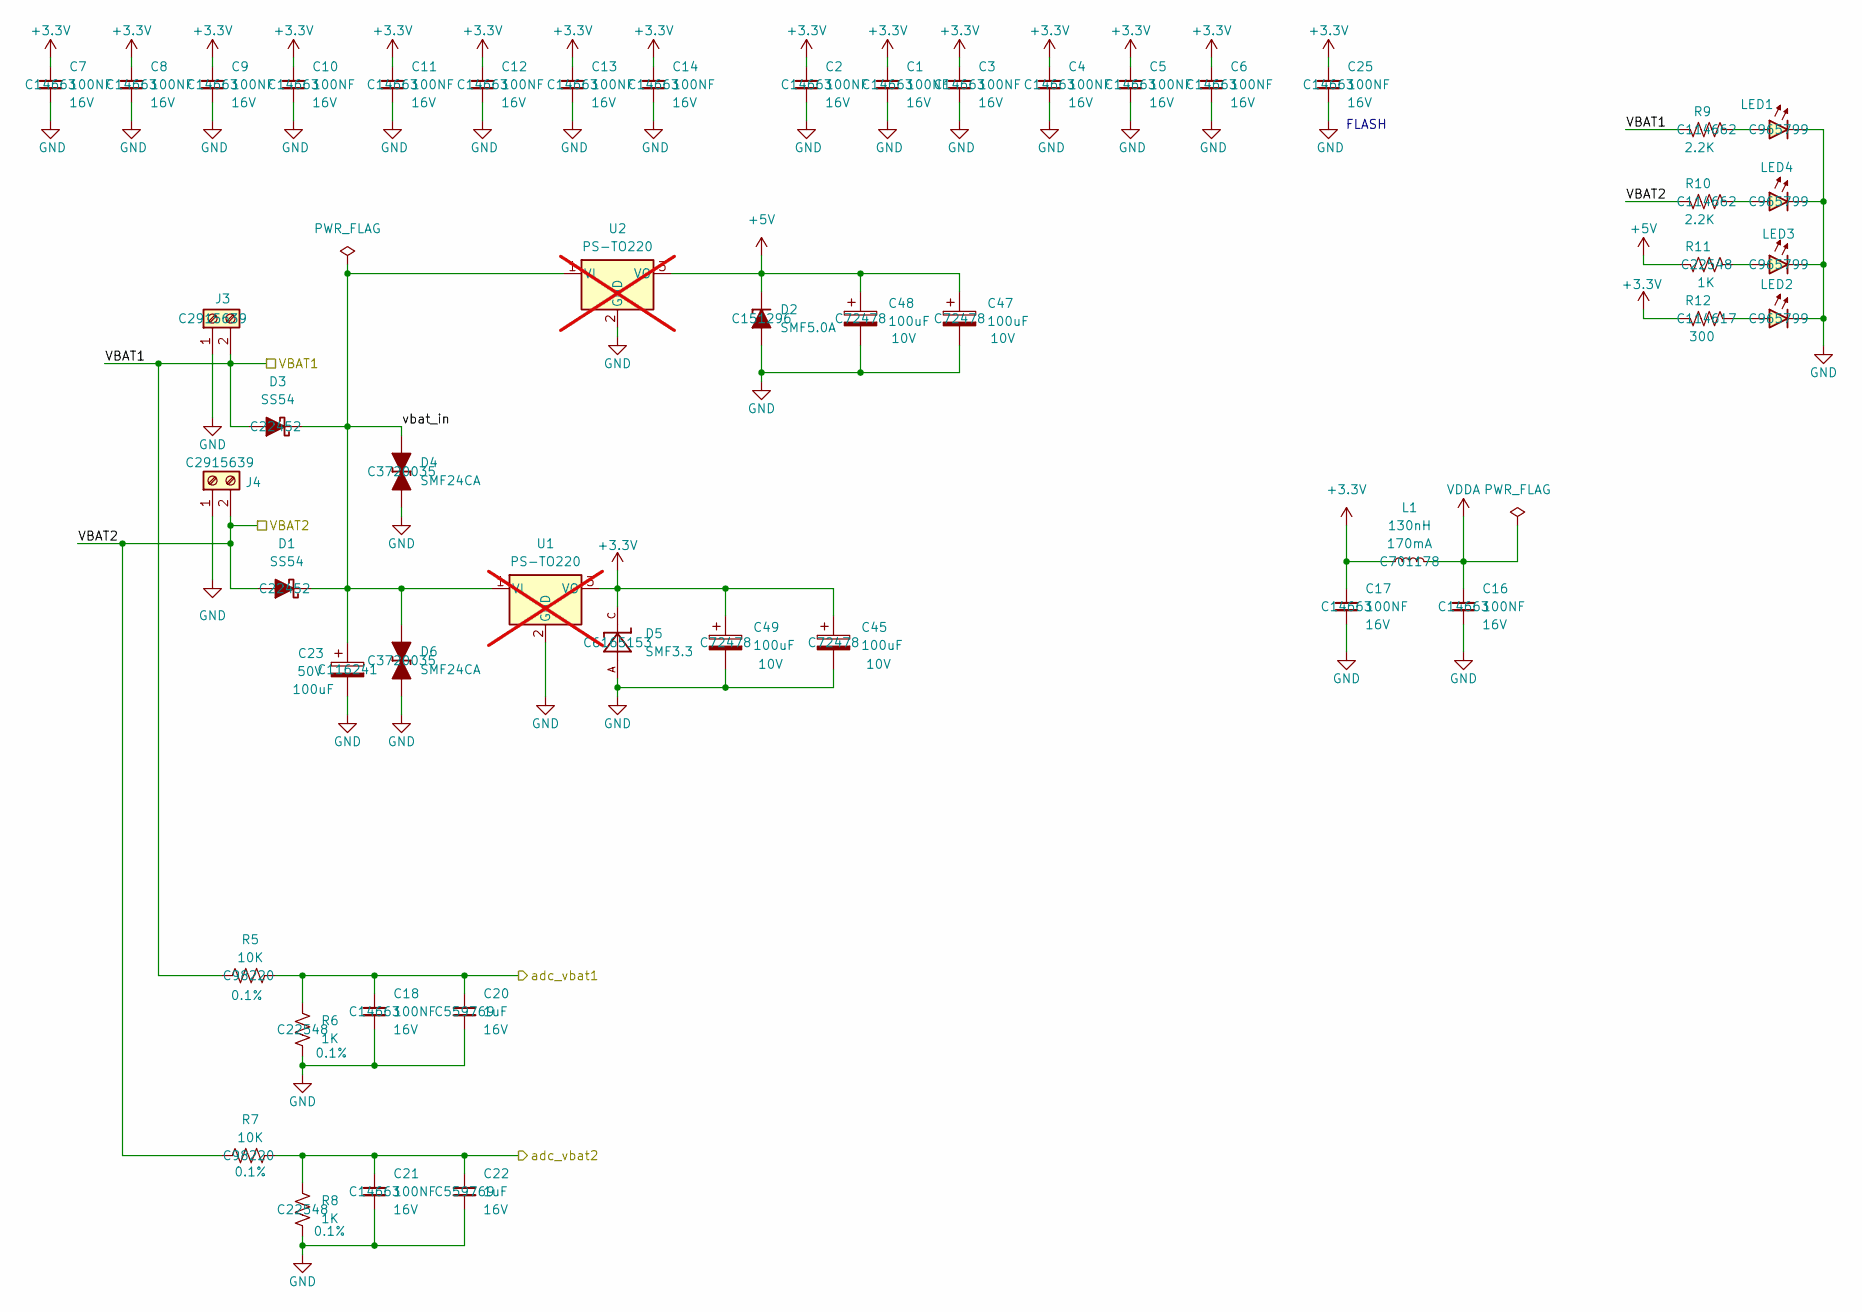
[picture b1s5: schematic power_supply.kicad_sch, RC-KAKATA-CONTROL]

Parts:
C1, C2, C3, C4, C5, C6, C7, C8, C9, C10, C11, C12, C13, C14, C16, C17, C18, C21, C25: 100NF; C_0603; Part Number 0603YC104KAT2A; JLCPCB ID C14663
C20, C22: 1uF; C_0603; Part Number 0603YC104KAT2A; JLCPCB ID C14663
C23: 100uF; CP_Elec_8x6.2; LCSC Part C116241
C45, C47, C48, C49: 100uF; CP_Elec_6.3x5.9; LCSC Part C72478
D1, D3: SS54; D_SMC; LCSC Part C22452
D2: SMF5.0A; D_SOD-123F; LCSC Part C151296
D4, D6: SMF24CA; D_SOD-123F; LCSC Part C3720035
D5: SMF3.3; SMF3.3_SODFL3718X108N; LCSC Part C6165153
J3, J4: Screw_Terminal_01x02; CONN-TH_2P-P5.08_DIBO_DB128V-5.08; LCSC Part C2915639
L1: 130nH; C_0603_1608Metric; LCSC Part C701178
LED1, LED2, LED3, LED4: LED_0603_Red; LED_0603_1608Metric; LCSC Part C965799
R5, R7: 10K; R_0603; Part Number RC0603FR-0710KL; LCSC Part C98220
R6, R8, R11: 1K; R_0603; Part Number RC0603FR-0710KL; LCSC Part C22548
R9, R10: 2.2K; R_0603; Part Number RC0603FR-0710KL; LCSC Part C114662
R12: 300; R_0603; Part Number RC0603FR-0710KL; LCSC Part C114617
U1, U2: PS-TO220; PS-TO-220-3_Vertical; not fitted

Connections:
+3.3V: C1.1, C2.1, C3.1, C4.1, C5.1, C6.1, C7.1, C8.1, C9.1, C10.1, C11.1, C12.1, C13.1, C14.1, C17.1, C25.1, C45.1, C49.1, D5.C, L1.1, R12.1, U1.3 (VO); also elsewhere on the board
+5V: C47.1, C48.1, D2.1 (K), R11.1, U2.3 (VO); also elsewhere on the board
/ADC_VBAT1: C18.1, C20.1, R5.2, R6.2; also elsewhere on the board
/ADC_VBAT2: C21.1, C22.1, R7.2, R8.2; also elsewhere on the board
/VBAT_1: D3.2 (A), J3.2, R5.1, R9.1; also elsewhere on the board
/VBAT_2: D1.2 (A), J4.2, R7.1, R10.1; also elsewhere on the board
/power_supply/vbat_in: C23.1, D1.1 (K), D3.1 (K), D4.2 (A), D6.2 (A), U1.1 (VI), U2.1 (VI)
GND: C1.2, C2.2, C3.2, C4.2, C5.2, C6.2, C7.2, C8.2, C9.2, C10.2, C11.2, C12.2, C13.2, C14.2, C16.2, C17.2, C18.2, C20.2, C21.2, C22.2, C23.2, C25.2, C45.2, C47.2, C48.2, C49.2, D2.2 (A), D4.1 (K), D5.A, D6.1 (K), J3.1, J4.1, LED1.1 (K), LED2.1 (K), LED3.1 (K), LED4.1 (K), R6.1, R8.1, U1.2 (GND), U2.2 (GND); also elsewhere on the board
unnamed: LED1.2 (A), R9.2
unnamed: LED2.2 (A), R12.2
unnamed: LED3.2 (A), R11.2
unnamed: LED4.2 (A), R10.2
VDDA: C16.1, L1.2; also elsewhere on the board

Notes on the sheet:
FLASH

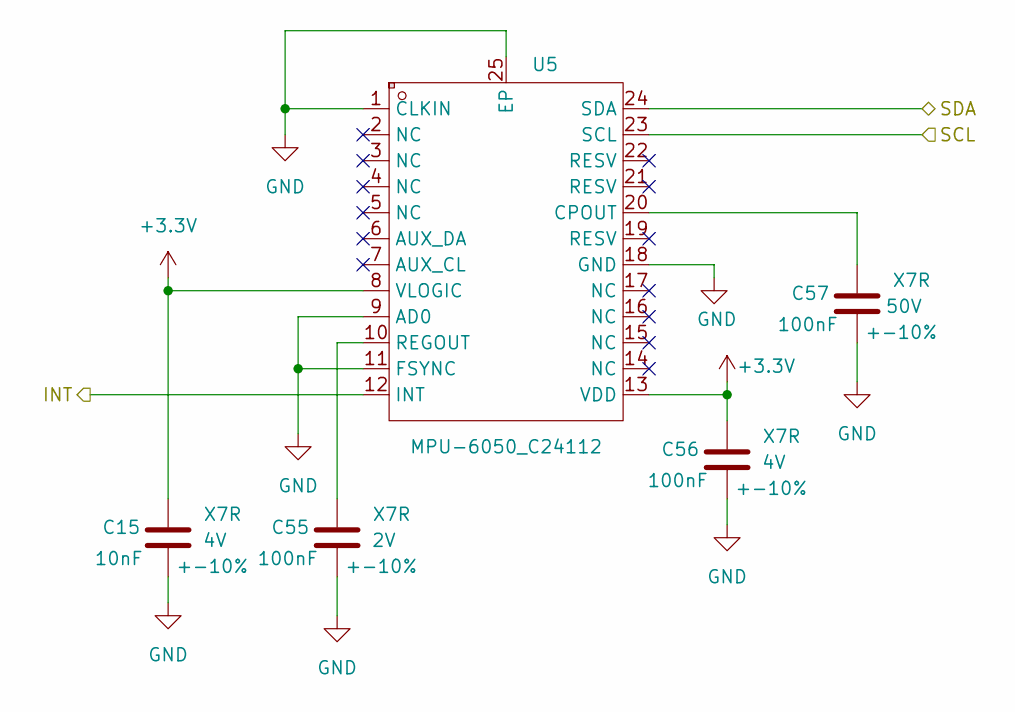
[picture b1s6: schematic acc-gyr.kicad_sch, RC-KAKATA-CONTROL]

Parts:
C15: 10nF; C_0603_1608Metric; LCSC Part C100042
C55, C56: 100nF; C_0603_1608Metric; LCSC Part C519438
C57: 100nF; C_0603_1608Metric; LCSC Part C14663
U5: MPU-6050_C24112; QFN-24_L4.0-W4.0-P0.50-BL-EP2.7; LCSC Part C24112

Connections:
+3.3V: C15.1, C56.1, U5.8 (VLOGIC), U5.13 (VDD); also elsewhere on the board
/ACC_GYR_INT: U5.12 (INT); also elsewhere on the board
/ACC_GYR_SCL: U5.23 (SCL); also elsewhere on the board
/ACC_GYR_SDA: U5.24 (SDA); also elsewhere on the board
GND: C15.2, C55.2, C56.2, C57.2, U5.1 (CLKIN), U5.9 (AD0), U5.11 (FSYNC), U5.18 (GND), U5.25 (EP); also elsewhere on the board
unnamed: C57.1, U5.20 (CPOUT)
unnamed: C55.1, U5.10 (REGOUT)
